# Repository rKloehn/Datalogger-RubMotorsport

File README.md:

# Datalogger-RubMotorsport

## Overview

For all RUB-Motorsport vehicles it makes sense to install a data logger in the vehicle. This can access and log all engine data (from the MS3) and all sensor data via the CAN bus. Up to now, RUBMotorsport has used a purchased data logger from 2D. This works well and has worked reliably over the years. However, only one data logger is available, due to the very high purchase price and the relatively easy installation in new vehicles, a new purchase was not made. The big disadvantage of this data logger is the software that comes with it. This must be used to export data from the data logger in e.g. *.csv files. The software license must be renewed every year, at the latest in February for one year. For the renewal of the license there is an annual fee of 500€. Due to the reasons mentioned above, in the 2020 season we will develop our own data logger based on a STM32F405RG. This should have all the previous functions of the 2D data logger and at a later date can also be integrated into the planned telemetry concept. 

The data logger has several connections to the outside world. These include the power supply of 12V, the connection to a GPS antenna, the possibility to process four sensor analog signals and supply them with voltage and the measurement of acceleration using an IMU. The option to store the measurement data on a microSD card is also part of the peripherals.

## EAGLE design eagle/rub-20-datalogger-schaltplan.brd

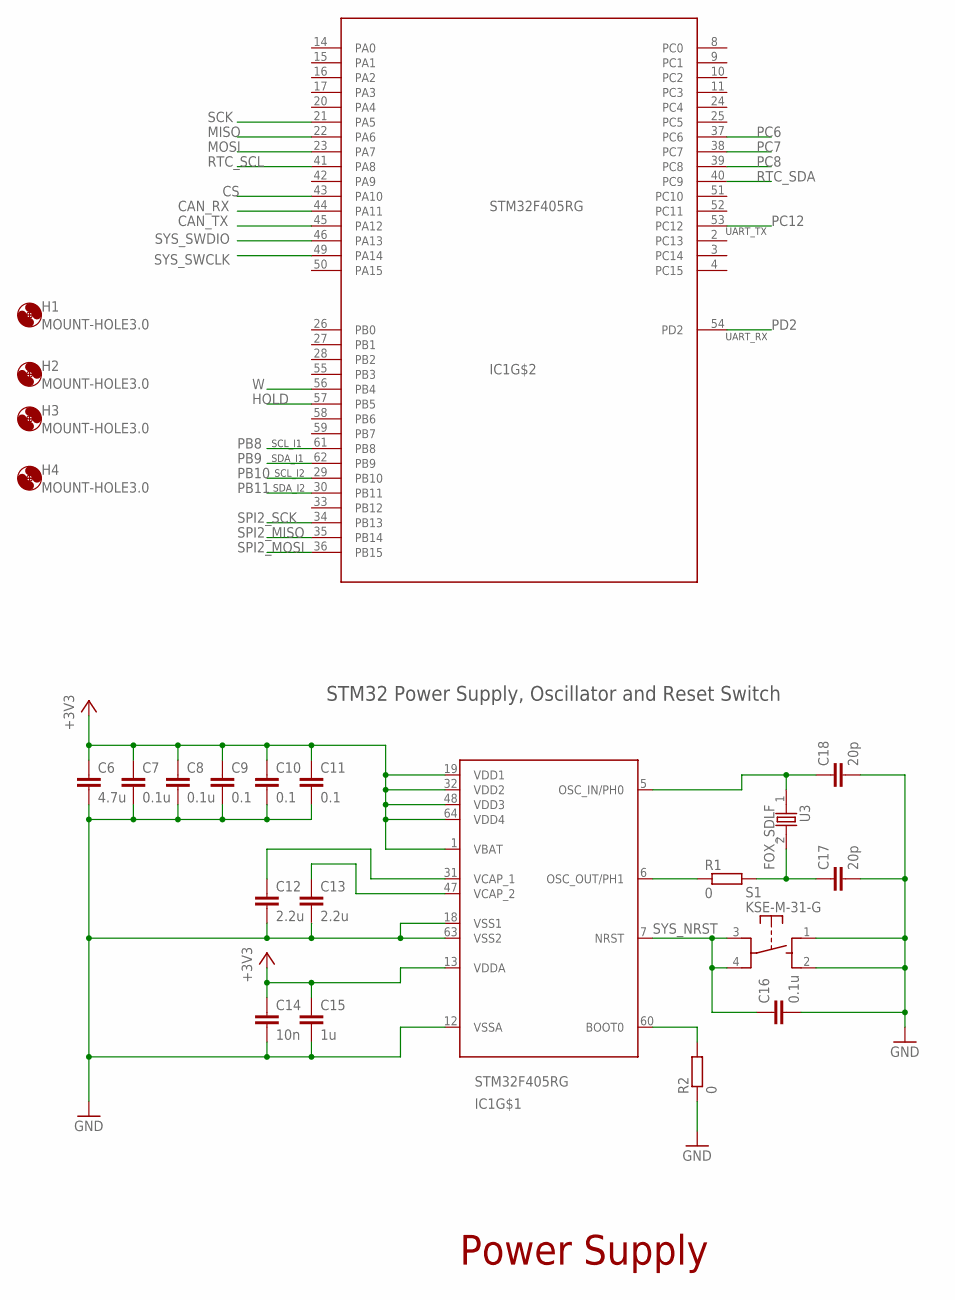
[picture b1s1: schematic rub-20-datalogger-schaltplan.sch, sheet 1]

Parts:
C6: 4.7u; C0805
C7, C8, C16: 0.1u; C0805
C9, C10, C11: 0.1; C0805
C12, C13: 2.2u; C0805
C14: 10n; C0805
C15: 1u; C0805
C17, C18: 20p; C0805
H1, H2, H3, H4: MOUNT-HOLE3.0; 3,0
IC1: STM32F405RG; LQFP64
R1, R2: 0; R0805
S1: KSE-M-31-G
U3: FOX_SDLF; HC49SSDLF

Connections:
+3V3: C6.1, C7.1, C8.1, C9.1, C10.1, C11.1, C14.1, C15.1, IC1.1 (VBAT), IC1.13 (VDDA), IC1.19 (VDD1), IC1.32 (VDD2), IC1.48 (VDD3), IC1.64 (VDD4); also elsewhere on the board
CAN_RX: IC1.44 (PA11); also elsewhere on the board
CAN_TX: IC1.45 (PA12); also elsewhere on the board
CS: IC1.43 (PA10); also elsewhere on the board
GND: C6.2, C7.2, C8.2, C9.2, C10.2, C11.2, C12.2, C13.2, C14.2, C15.2, C16.2, C17.2, C18.2, IC1.12 (VSSA), IC1.18 (VSS1), IC1.63 (VSS2), R2.1, S1.1, S1.2; also elsewhere on the board
HOLD: IC1.57 (PB5); also elsewhere on the board
MISO: IC1.22 (PA6); also elsewhere on the board
MOSI: IC1.23 (PA7); also elsewhere on the board
unnamed: C13.1, IC1.47 (VCAP_2)
unnamed: C12.1, IC1.31 (VCAP_1)
unnamed: IC1.60 (BOOT0), R2.2
unnamed: IC1.6 (OSC_OUT/PH1), R1.1
unnamed: C17.1, R1.2, U3.2
unnamed: C18.1, IC1.5 (OSC_IN/PH0), U3.1
PB8: IC1.61 (PB8); also elsewhere on the board
PB9: IC1.62 (PB9); also elsewhere on the board
PB10: IC1.29 (PB10); also elsewhere on the board
PB11: IC1.30 (PB11); also elsewhere on the board
PC6: IC1.37 (PC6); also elsewhere on the board
PC7: IC1.38 (PC7); also elsewhere on the board
PC8: IC1.39 (PC8); also elsewhere on the board
PC12: IC1.53 (PC12); also elsewhere on the board
PD2: IC1.54 (PD2); also elsewhere on the board
RTC_SCL: IC1.41 (PA8); also elsewhere on the board
RTC_SDA: IC1.40 (PC9); also elsewhere on the board
SCK: IC1.21 (PA5); also elsewhere on the board
SPI2_MISO: IC1.35 (PB14); also elsewhere on the board
SPI2_MOSI: IC1.36 (PB15); also elsewhere on the board
SPI2_SCK: IC1.34 (PB13); also elsewhere on the board
SYS_NRST: C16.1, IC1.7 (NRST), S1.3, S1.4; also elsewhere on the board
SYS_SWCLK: IC1.49 (PA14); also elsewhere on the board
SYS_SWDIO: IC1.46 (PA13); also elsewhere on the board
W: IC1.56 (PB4); also elsewhere on the board

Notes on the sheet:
Power Supply
STM32 Power Supply, Oscillator and Reset Switch
SCL_I1
SDA_I1
UART_RX
UART_TX
SCL_I2
SDA_I2

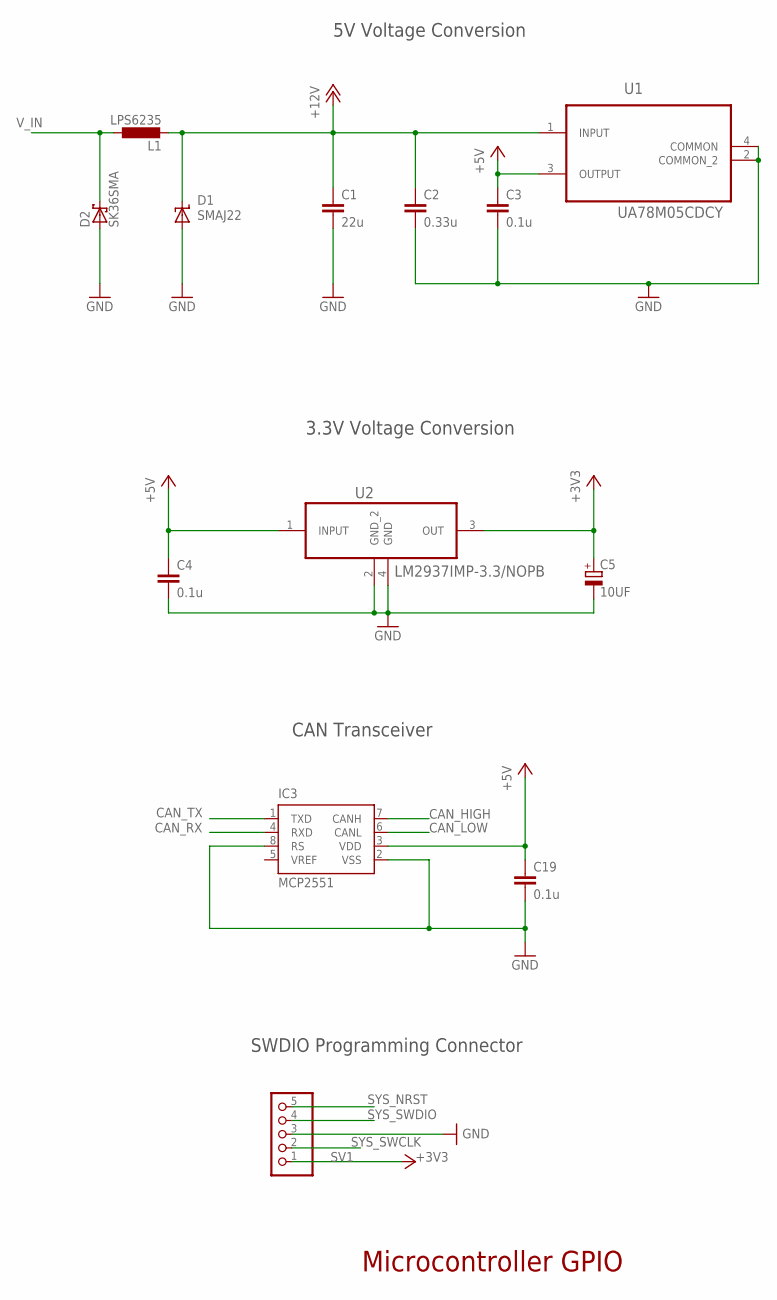
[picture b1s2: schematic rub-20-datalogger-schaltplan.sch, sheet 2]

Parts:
C1: 22u; C1812K
C2: 0.33u; C0805
C3, C4, C19: 0.1u; C0805
C5: 10UF; CAPAE430X610N
D1: SMAJ22; SMA-DO214AC
D2: SK36SMA; DO214AC
IC3: MCP2551; 8SO
L1: LPS6235
SV1: PINHD-1X5; 1X05
U1: UA78M05CDCY; SOT230P700X180-4N
U2: LM2937IMP-3.3/NOPB; SOT230P700X180-4N

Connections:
+3V3: C5.1 (+), SV1.1, U2.3 (OUT); also elsewhere on the board
+5V: C3.1, C4.1, C19.1, IC3.3 (VDD), U1.3 (OUTPUT), U2.1 (INPUT); also elsewhere on the board
+12V: C1.1, C2.1, D1.K (C), L1.2, U1.1 (INPUT); also elsewhere on the board
CAN_HIGH: IC3.7 (CANH); also elsewhere on the board
CAN_LOW: IC3.6 (CANL); also elsewhere on the board
CAN_RX: IC3.4 (RXD); also elsewhere on the board
CAN_TX: IC3.1 (TXD); also elsewhere on the board
GND: C1.2, C2.2, C3.2, C4.2, C5.2 (-), C19.2, D1.A, D2.A, IC3.2 (VSS), IC3.8 (RS), SV1.3, U1.2 (COMMON_2), U1.4 (COMMON), U2.2 (GND_2), U2.4 (GND); also elsewhere on the board
SYS_NRST: SV1.5; also elsewhere on the board
SYS_SWCLK: SV1.2; also elsewhere on the board
SYS_SWDIO: SV1.4; also elsewhere on the board
V_IN: D2.C, L1.1; also elsewhere on the board

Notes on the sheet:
CAN Transceiver
Microcontroller GPIO
SWDIO Programming Connector
3.3V Voltage Conversion
5V Voltage Conversion

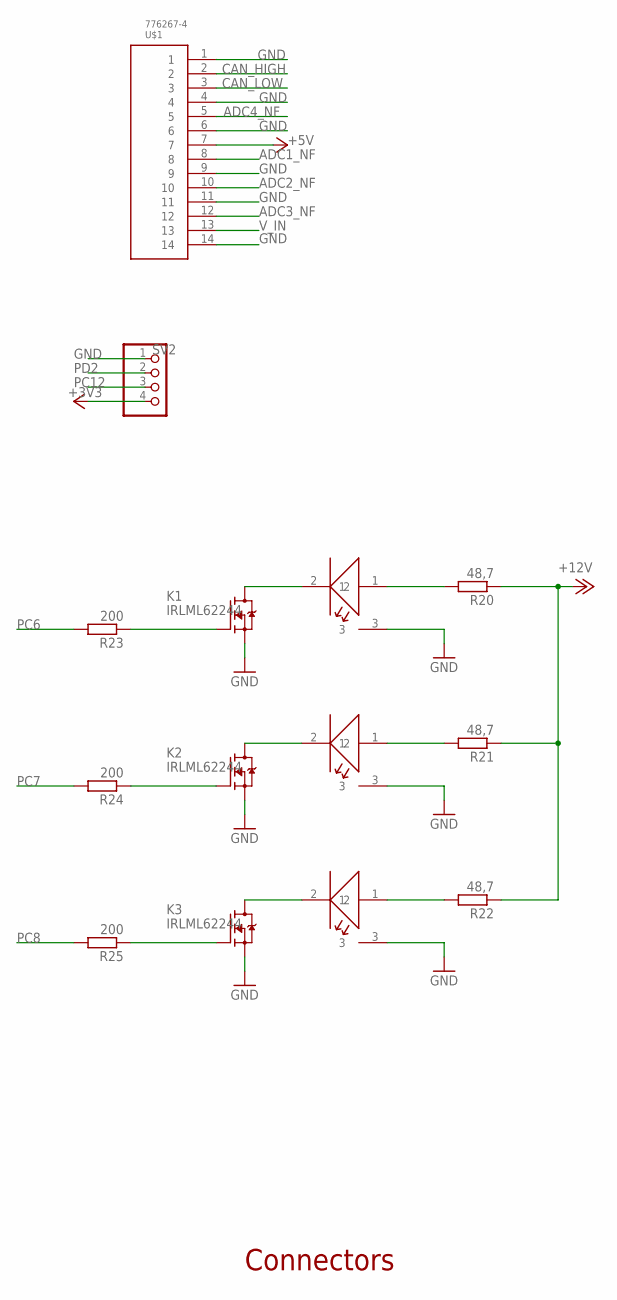
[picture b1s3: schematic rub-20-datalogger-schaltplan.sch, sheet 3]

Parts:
K1, K2, K3: IRLML62244; SOT23-MICRO
P1, P2, P3: XLAMP_ML-E; CREE_XLAMP_ML-E
R20, R21, R22: 48,7; R0805
R23, R24, R25: 200; R0805
SV2: PINHD-1X4; 1X04
U$1: 776267-4; TE_776267-4

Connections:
+3V3: SV2.4; also elsewhere on the board
+5V: U$1.7; also elsewhere on the board
+12V: R20.1, R21.1, R22.1; also elsewhere on the board
ADC1_NF: U$1.8; also elsewhere on the board
ADC2_NF: U$1.10; also elsewhere on the board
ADC3_NF: U$1.12; also elsewhere on the board
ADC4_NF: U$1.5; also elsewhere on the board
CAN_HIGH: U$1.2; also elsewhere on the board
CAN_LOW: U$1.3; also elsewhere on the board
GND: K1.2 (S), K2.2 (S), K3.2 (S), P1.3, P2.3, P3.3, SV2.1, U$1.1, U$1.4, U$1.6, U$1.9, U$1.11, U$1.14; also elsewhere on the board
unnamed: P2.1, R21.2
unnamed: P1.1, R20.2
unnamed: P3.1, R22.2
unnamed: K1.1 (G), R23.1
unnamed: K2.1 (G), R24.1
unnamed: K3.1 (G), R25.1
unnamed: K1.3 (D), P1.2
unnamed: K2.3 (D), P2.2
unnamed: K3.3 (D), P3.2
PC6: R23.2; also elsewhere on the board
PC7: R24.2; also elsewhere on the board
PC8: R25.2; also elsewhere on the board
PC12: SV2.3; also elsewhere on the board
PD2: SV2.2; also elsewhere on the board
V_IN: U$1.13; also elsewhere on the board

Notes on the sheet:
Connectors

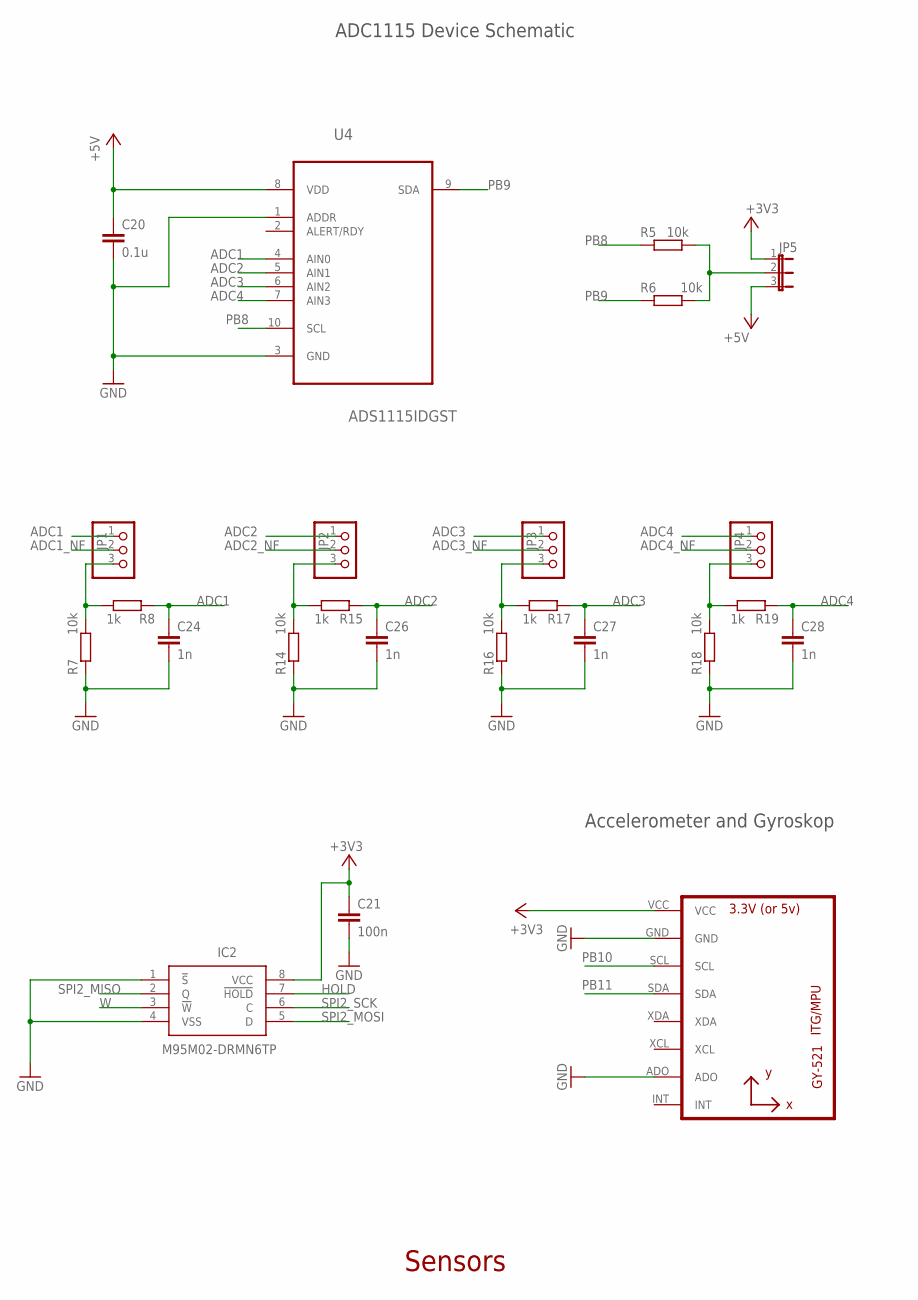
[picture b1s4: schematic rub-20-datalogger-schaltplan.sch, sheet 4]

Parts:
C20: 0.1u; C0805
C21: 100n; C0805
C24, C26, C27, C28: 1n; C0805
IC2: M95M02-DRMN6TP; SOIC127P600X175-8N
JP1, JP2, JP3, JP4: PINHD-1X3; 1X03
JP5: JP2E; JP2
R5, R6, R7, R14, R16, R18: 10k; R0805
R8, R15, R17, R19: 1k; R0805
U4: ADS1115IDGST; SOP50P490X110-10N
U6: GY-521MPU6050; GY-521

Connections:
+3V3: C21.1, IC2.8 (VCC), JP5.1, U6.VCC; also elsewhere on the board
+5V: C20.1, JP5.3, U4.8 (VDD); also elsewhere on the board
ADC1: C24.1, JP1.1, R8.2, U4.4 (AIN0)
ADC1_NF: JP1.2; also elsewhere on the board
ADC2: C26.1, JP2.1, R15.2, U4.5 (AIN1)
ADC2_NF: JP2.2; also elsewhere on the board
ADC3: C27.1, JP3.1, R17.2, U4.6 (AIN2)
ADC3_NF: JP3.2; also elsewhere on the board
ADC4: C28.1, JP4.1, R19.2, U4.7 (AIN3)
ADC4_NF: JP4.2; also elsewhere on the board
GND: C20.2, C21.2, C24.2, C26.2, C27.2, C28.2, IC2.1 (!S), IC2.4 (VSS), R7.2, R14.2, R16.2, R18.2, U4.1 (ADDR), U4.3 (GND), U6.ADO, U6.GND; also elsewhere on the board
HOLD: IC2.7 (!HOLD); also elsewhere on the board
unnamed: JP1.3, R7.1, R8.1
unnamed: JP2.3, R14.1, R15.1
unnamed: JP3.3, R16.1, R17.1
unnamed: JP4.3, R18.1, R19.1
unnamed: JP5.2, R5.1, R6.1
PB8: R5.2, U4.10 (SCL); also elsewhere on the board
PB9: R6.2, U4.9 (SDA); also elsewhere on the board
PB10: U6.SCL; also elsewhere on the board
PB11: U6.SDA; also elsewhere on the board
SPI2_MISO: IC2.2 (Q); also elsewhere on the board
SPI2_MOSI: IC2.5 (D); also elsewhere on the board
SPI2_SCK: IC2.6 (C); also elsewhere on the board
W: IC2.3 (!W); also elsewhere on the board

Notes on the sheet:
ADC1115 Device Schematic
Accelerometer and Gyroskop
Sensors

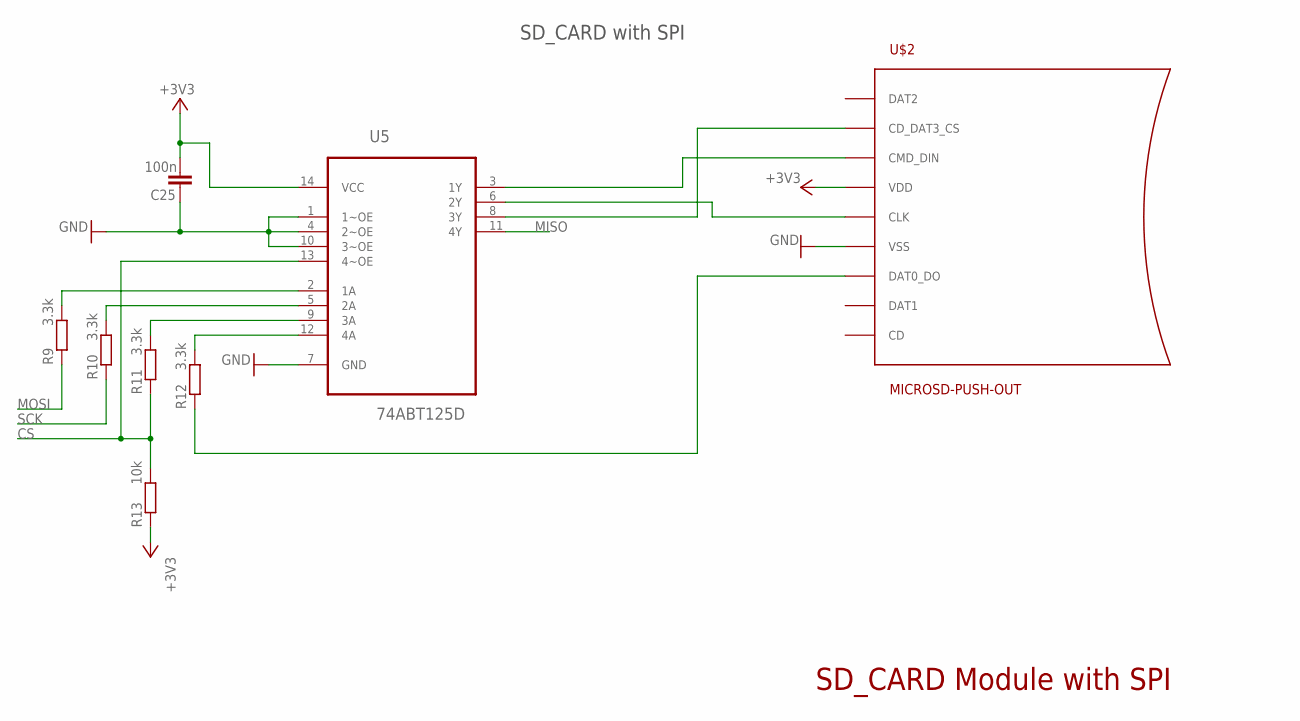
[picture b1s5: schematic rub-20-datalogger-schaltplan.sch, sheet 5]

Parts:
C25: 100n; C0805
R9, R10, R11, R12: 3.3k; R0805
R13: 10k; R0805
U5: 74ABT125D; SOIC127P600X175-14N
U$2: MICROSD-PUSH-OUT

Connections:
+3V3: C25.2, R13.2, U5.14 (VCC), U$2.4 (VDD); also elsewhere on the board
CS: R11.2, R13.1, U5.13 (4~OE); also elsewhere on the board
GND: C25.1, U5.1 (1~OE), U5.4 (2~OE), U5.7 (GND), U5.10 (3~OE), U$2.6 (VSS), U$2.G1 (VSS), U$2.G2 (VSS), U$2.G3 (VSS), U$2.G4 (VSS); also elsewhere on the board
MISO: U5.11 (4Y); also elsewhere on the board
MOSI: R9.2; also elsewhere on the board
unnamed: R9.1, U5.2 (1A)
unnamed: U5.8 (3Y), U$2.2 (CD_DAT3_CS)
unnamed: U5.3 (1Y), U$2.3 (CMD_DIN)
unnamed: U5.6 (2Y), U$2.5 (CLK)
unnamed: R12.1, U5.12 (4A)
unnamed: R10.1, U5.5 (2A)
unnamed: R11.1, U5.9 (3A)
unnamed: R12.2, U$2.7 (DAT0_DO)
SCK: R10.2; also elsewhere on the board

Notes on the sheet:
SD_CARD Module with SPI
SD_CARD with SPI

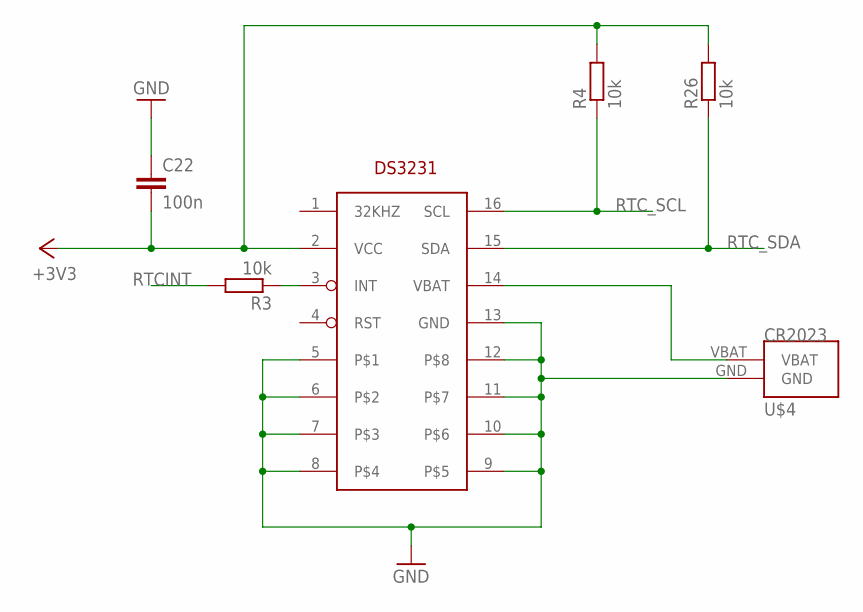
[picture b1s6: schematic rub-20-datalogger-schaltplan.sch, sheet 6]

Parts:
C22: 100n; C0805
R3, R4, R26: 10k; R0805
U$3: DS3231; SO16
U$4: CR2023; STMU2023-G

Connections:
+3V3: C22.2, R4.2, R26.2, U$3.2 (VCC); also elsewhere on the board
GND: C22.1, U$3.5, U$3.6, U$3.7, U$3.8, U$3.9, U$3.10, U$3.11, U$3.12, U$3.13 (GND), U$4.GND; also elsewhere on the board
unnamed: U$3.14 (VBAT), U$4.VBAT
unnamed: R3.1, U$3.3 (INT)
RTCINT: R3.2
RTC_SCL: R4.1, U$3.16 (SCL); also elsewhere on the board
RTC_SDA: R26.1, U$3.15 (SDA); also elsewhere on the board

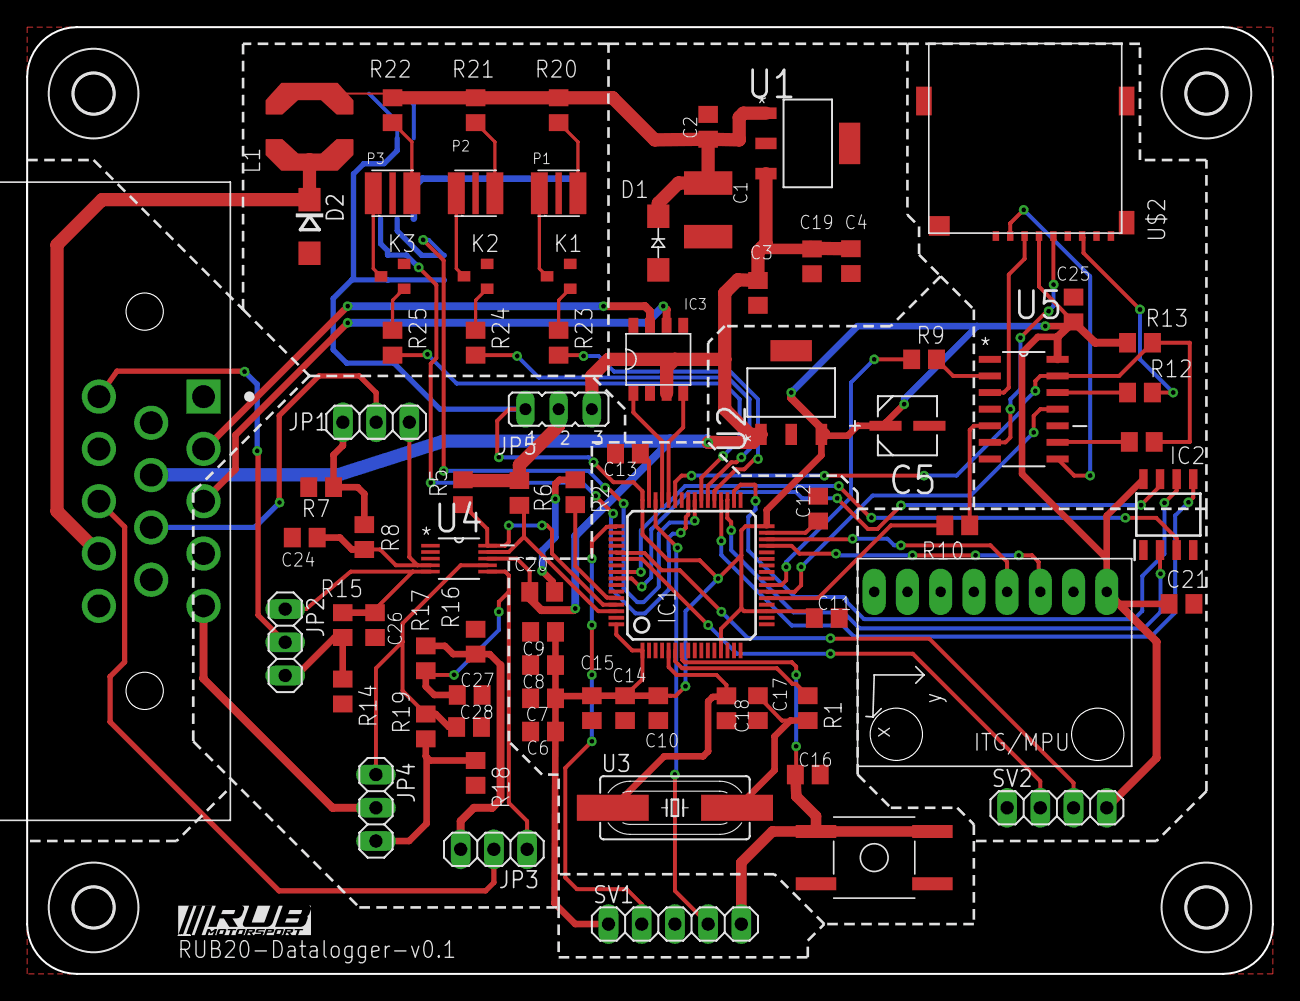
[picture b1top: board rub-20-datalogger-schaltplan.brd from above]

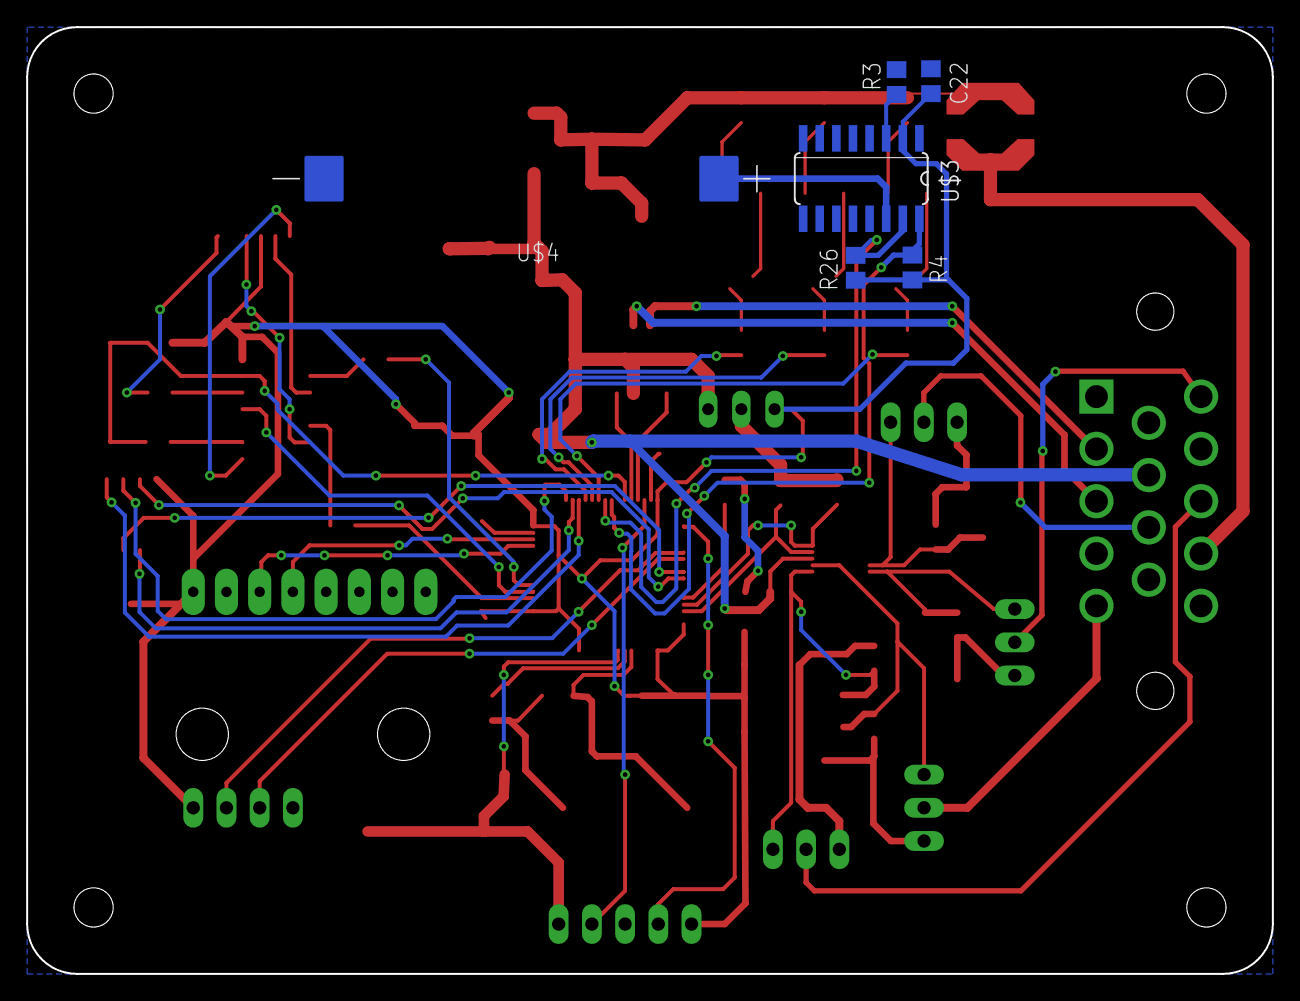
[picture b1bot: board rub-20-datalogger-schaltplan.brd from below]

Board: 2 copper layers, 95.2 x 72.4 mm, 87 parts (6 on the bottom side), 70 nets.

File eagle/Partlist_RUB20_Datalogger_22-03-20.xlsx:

Part | Value | Package | Library | Bestellnummer
C1 | 22u | C1812K | rcl
C2 | 0.33u | C0805 | rcl
C3 | 0.1u | C0805 | rcl
C4 | 0.1u | C0805 | rcl
C5 | 10UF | CAPAE430X610N | Panasonic-EEEFK_EEEFP
C6 | 4.7u | C0805 | rcl
C7 | 0.1u | C0805 | rcl
C8 | 0.1u | C0805 | rcl
C9 | 0.1 | C0805 | rcl
C10 | 0.1 | C0805 | rcl
C11 | 0.1 | C0805 | rcl
C12 | 2.2u | C0805 | rcl
C13 | 2.2u | C0805 | rcl
C14 | 10n | C0805 | rcl
C15 | 1u | C0805 | rcl
C16 | 0.1u | C0805 | rcl
C17 | 20p | C0805 | rcl
C18 | 20p | C0805 | rcl
C19 | 0.1u | C0805 | rcl
C20 | 0.1u | C0805 | rcl
C21 | 100n | C0805 | rcl
C24 | 1n | C0805 | rcl
C25 | 100n | C0805 | rcl
C26 | 1n | C0805 | rcl
C27 | 1n | C0805 | rcl
C28 | 1n | C0805 | rcl
D1 | SMAJ22 | SMA-DO214AC | RUBM_PARTS
D2 | SK36SMA | DO214AC | RUBM_PARTS
IC1 | STM32F405RG | LQFP64 | RUBM_PARTS
IC2 | M95M02-DRMN6TP | SOIC127P600X175-8N | SamacSys_Parts
IC3 | MCP2551 | 8SO | RUBM_PARTS
JP1 | 1X03 | pinhead | (1050
JP2 | 1X03 | pinhead | (776.79995
JP3 | 1X03 | pinhead | (1405
JP4 | 1X03 | pinhead | (1050
JP5 | JP2 | jumper | (1600
K1 | IRLML62244 | SOT23-MICRO | RUBM_PARTS
K2 | IRLML62244 | SOT23-MICRO | RUBM_PARTS
K3 | IRLML62244 | SOT23-MICRO | RUBM_PARTS
L1 | LPS6235 | LPS6235 | RUBM_PARTS
P1 | XLAMP_ML-E | CREE_XLAMP_ML-E | RUBM_PARTS
P2 | XLAMP_ML-E | CREE_XLAMP_ML-E | RUBM_PARTS
P3 | XLAMP_ML-E | CREE_XLAMP_ML-E | RUBM_PARTS
R1 | 0 | R0805 | rcl
R2 | 0 | R0805 | rcl
R5 | 10k | R0805 | rcl
R6 | 10k | R0805 | rcl
R7 | 10k | R0805 | rcl
R8 | 1k | R0805 | rcl
R9 | 3.3k | R0805 | rcl
R10 | 3.3k | R0805 | rcl
R11 | 3.3k | R0805 | rcl
R12 | 3.3k | R0805 | rcl
R13 | 10k | R0805 | rcl
R14 | 10k | R0805 | rcl
R15 | 1k | R0805 | rcl
R16 | 10k | R0805 | rcl
R17 | 1k | R0805 | rcl
R18 | 10k | R0805 | rcl
R19 | 1k | R0805 | rcl
R20 | 48.7 | R0805 | rcl
R21 | 48.7 | R0805 | rcl
R22 | 48.7 | R0805 | rcl
R23 | 200 | R0805 | rcl
R24 | 200 | R0805 | rcl
R25 | 200 | R0805 | rcl
S1 | KSE-M-31-G | KSE-M-31-G | RUBM_PARTS
SV1 | 1X05 | pinhead | (1950
SV2 | 1X04 | pinhead | (3100
U$1 | 776267-4 | TE_776267-4 | 776267-4
U$2 | MICROSD-PUSH-OUT | MICROSD-PUSH-OUT | microsd
U1 | UA78M05CDCY | SOT230P700X180-4N | RUBM_PARTS
U2 | LM2937IMP-3.3/NOPB | SOT230P700X180-4N | RUBM_PARTS
U3 | FOX_SDLF | HC49SSDLF | RUBM_PARTS
U4 | ADS1115IDGST | SOP50P490X110-10N | Texas |  |  |  | R0
U5 | 74ABT125D | SOIC127P600X175-14N | NXP_By_element14_Batch_1
U6 | GY-521MPU6050 | GY-521 | gy-521_holes
